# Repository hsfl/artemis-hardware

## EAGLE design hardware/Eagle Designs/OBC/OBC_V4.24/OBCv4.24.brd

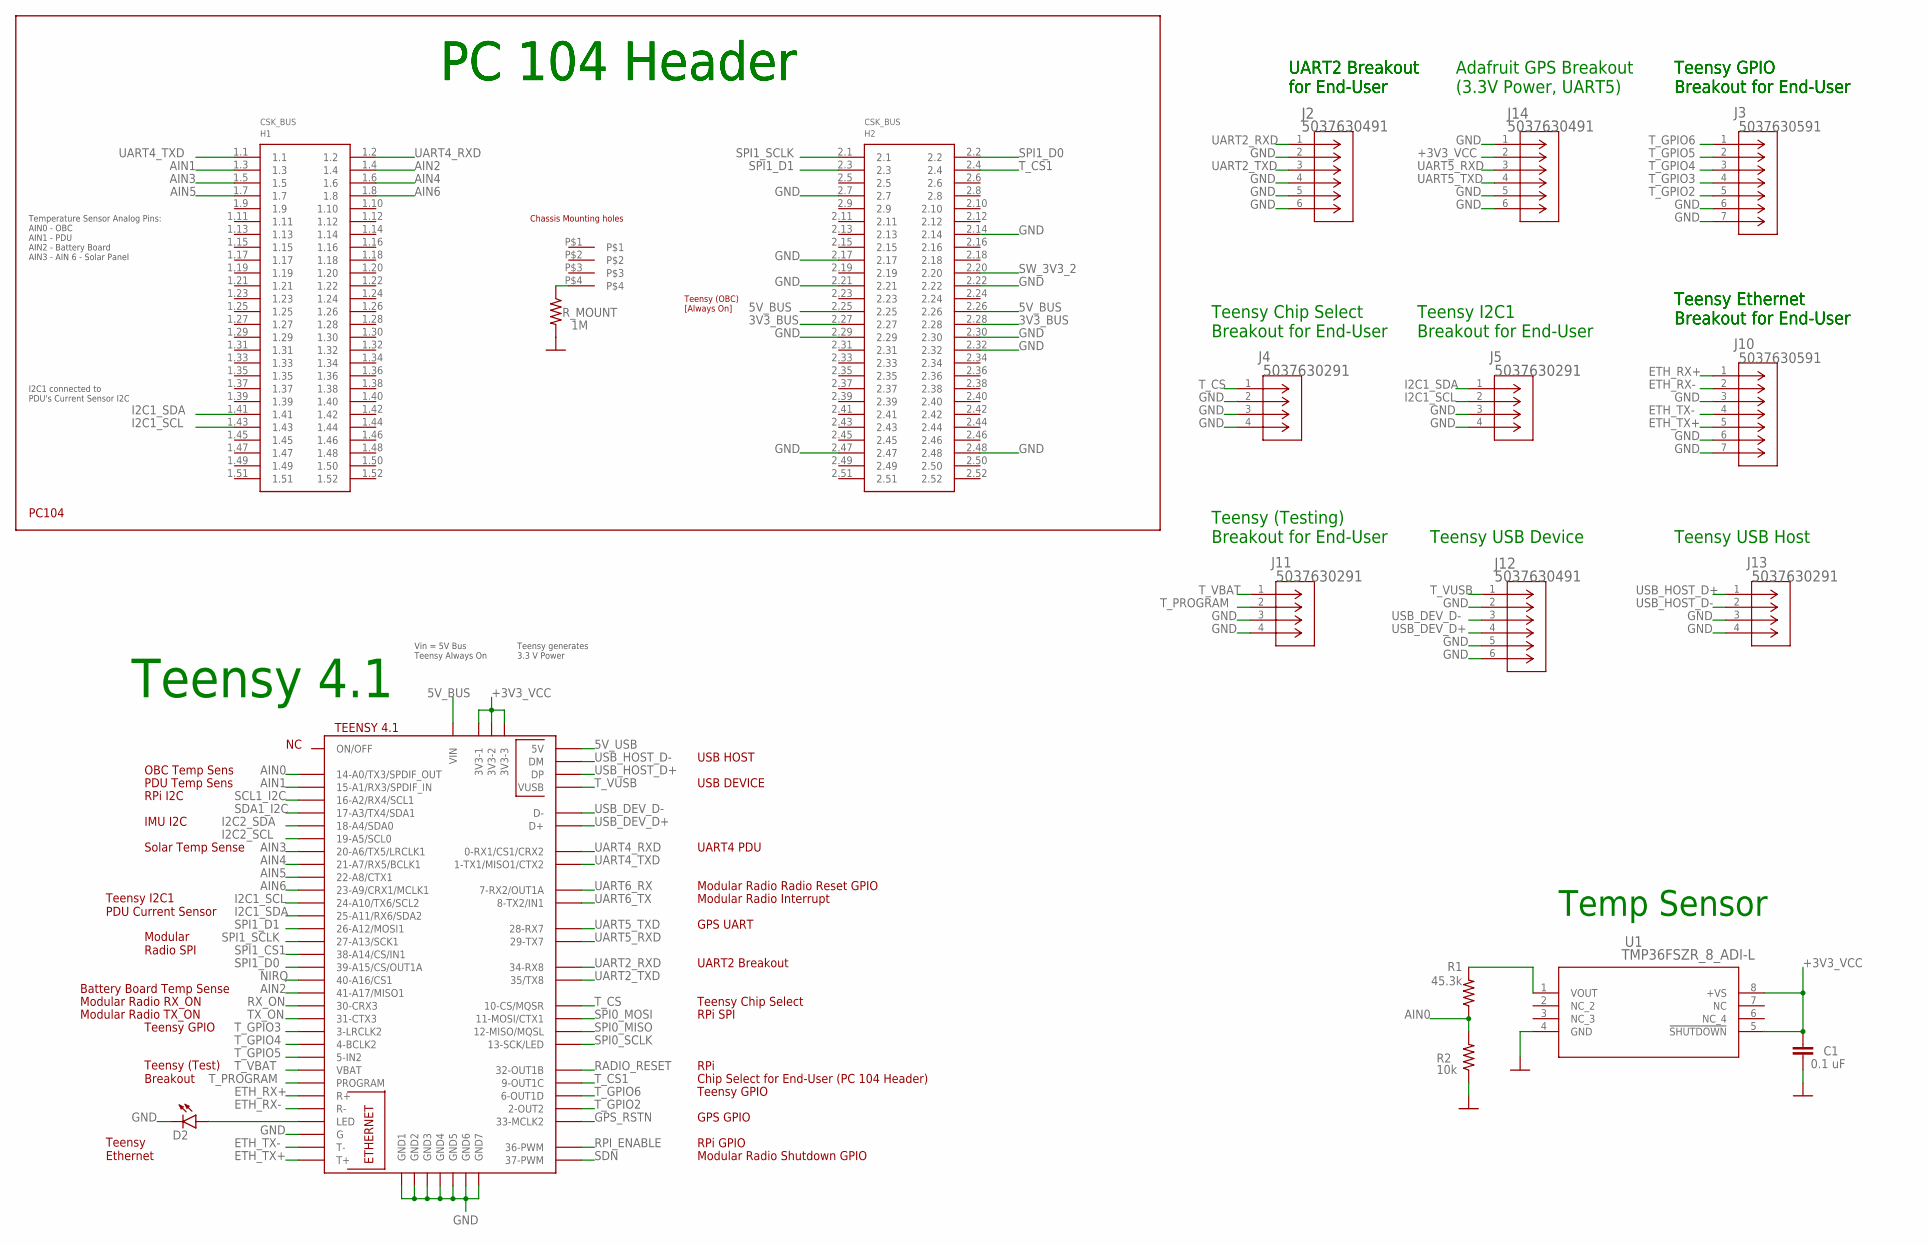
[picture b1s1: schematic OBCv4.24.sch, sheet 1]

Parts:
C1: 0.1 uF; 0805
D2: LEDCHIP-LED0603; CHIP-LED0603
H1: PC104_WCONN
J2, J12, J14: 5037630491; CON_5037630491
J3, J10: 5037630591; CON_5037630591
J4, J5, J11, J13: 5037630291; CON_5037630291
R1: 45.3k; 0805
R2: 10k; 0805
R_MOUNT: 1M; 0805
U1: TMP36FSZR_8_ADI-L; R_8_ADI-L
U$1: TEENSY41TEENSY; TEENSY41

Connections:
3V3_BUS: H1.2.27, H1.2.28; also elsewhere on the board
5V_BUS: H1.2.25, H1.2.26, U$1.VIN; also elsewhere on the board
5V_USB: U$1.+5V (5V)
+3V3_VCC: C1.1, J14.2, U1.5 (!SHUTDOWN), U1.8 (+VS), U$1.3V3-1, U$1.3V3-2, U$1.3V3-3; also elsewhere on the board
AIN0: R1.1, R2.2, U$1.14-A0/TX3/SPDIF_OUT
AIN1: H1.1.3, U$1.15-A1/RX3/SPDIF_IN
AIN2: H1.1.4, U$1.41-A17/MISO1
AIN3: H1.1.5, U$1.20-A6/TX5/LRCLK1
AIN4: H1.1.6, U$1.21-A7/RX5/BCLK1
AIN5: H1.1.7, U$1.22-A8/CTX1
AIN6: H1.1.8, U$1.23-A9/CRX1/MCLK1
ETH_RX+: J10.1, U$1.R+
ETH_RX-: J10.2, U$1.R-
ETH_TX+: J10.5, U$1.T+
ETH_TX-: J10.4, U$1.T-
GND: C1.2, D2.C, H1.2.7, H1.2.14, H1.2.17, H1.2.21, H1.2.22, H1.2.29, H1.2.30, H1.2.32, H1.2.47, H1.2.48, J2.2, J2.4, J2.5, J2.6, J3.6, J3.7, J4.2, J4.3, J4.4, J5.3, J5.4, J10.3, J10.6, J10.7, J11.3, J11.4, J12.2, J12.5, J12.6, J13.3, J13.4, J14.1, J14.5, J14.6, R2.1, R_MOUNT.2, U1.4 (GND), U$1.G, U$1.GND (GND7), U$1.GND1, U$1.GND2, U$1.GND3, U$1.GND4, U$1.GND5, U$1.GND6; also elsewhere on the board
GPS_RSTN: U$1.33-MCLK2; also elsewhere on the board
I2C1_SCL: H1.1.43, J5.2, U$1.24-A10/TX6/SCL2
I2C1_SDA: H1.1.41, J5.1, U$1.25-A11/RX6/SDA2
I2C2_SCL: U$1.19-A5/SCL0; also elsewhere on the board
I2C2_SDA: U$1.18-A4/SDA0; also elsewhere on the board
unnamed: D2.A, U$1.LED
unnamed: R1.2, U1.1 (VOUT)
unnamed: H1.P$4, R_MOUNT.1
NIRQ: U$1.40-A16/CS1; also elsewhere on the board
RADIO_RESET: U$1.32-OUT1B; also elsewhere on the board
RPI_ENABLE: U$1.36-PWM; also elsewhere on the board
RX_ON: U$1.30-CRX3; also elsewhere on the board
SCL1_I2C: U$1.16-A2/RX4/SCL1; also elsewhere on the board
SDA1_I2C: U$1.17-A3/TX4/SDA1; also elsewhere on the board
SDN: U$1.37-PWM; also elsewhere on the board
SPI0_MISO: U$1.12-MISO/MQSL; also elsewhere on the board
SPI0_MOSI: U$1.11-MOSI/CTX1; also elsewhere on the board
SPI0_SCLK: U$1.13-SCK/LED; also elsewhere on the board
SPI1_CS1: U$1.38-A14/CS/IN1; also elsewhere on the board
SPI1_D0: H1.2.2, U$1.39-A15/CS/OUT1A; also elsewhere on the board
SPI1_D1: H1.2.3, U$1.26-A12/MOSI1; also elsewhere on the board
SPI1_SCLK: H1.2.1, U$1.27-A13/SCK1; also elsewhere on the board
SW_3V3_2: H1.2.20; also elsewhere on the board
TX_ON: U$1.31-CTX3; also elsewhere on the board
T_CS: J4.1, U$1.10-CS\MQSR (10-CS/MQSR)
T_CS1: H1.2.4, U$1.9-OUT1C
T_GPIO2: J3.5, U$1.2-OUT2
T_GPIO3: J3.4, U$1.3-LRCLK2
T_GPIO4: J3.3, U$1.4-BCLK2
T_GPIO5: J3.2, U$1.5-IN2
T_GPIO6: J3.1, U$1.6-OUT1D
T_PROGRAM: J11.2, U$1.PROGRAM
T_VBAT: J11.1, U$1.VBAT
T_VUSB: J12.1, U$1.VUSB
UART2_RXD: J2.1, U$1.34-RX8
UART2_TXD: J2.3, U$1.35-TX8 (35/TX8)
UART4_RXD: H1.1.2, U$1.0-RX1/CS1/CRX2
UART4_TXD: H1.1.1, U$1.1-TX1/MISO1/CTX2
UART5_RXD: J14.3, U$1.29-TX7; also elsewhere on the board
UART5_TXD: J14.4, U$1.28-RX7; also elsewhere on the board
UART6_RX: U$1.7-RX2/OUT1A; also elsewhere on the board
UART6_TX: U$1.8-TX2/IN1; also elsewhere on the board
USB_DEV_D+: J12.4, U$1.D+
USB_DEV_D-: J12.3, U$1.D-
USB_HOST_D+: J13.1, U$1.DP
USB_HOST_D-: J13.2, U$1.DM

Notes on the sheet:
Temp Sensor
PC 104 Header
Temperature Sensor Analog Pins: AIN0 - OBC AIN1 - PDU AIN2 - Battery Board AIN3 - AIN 6 - Solar Panel
UART2 Breakout for End-User
Teensy 4.1
Teensy GPIO Breakout for End-User
Teensy Chip Select Breakout for End-User
Teensy I2C1 Breakout for End-User
OBC Temp Sens
PDU Temp Sens
RPi I2C
IMU I2C
Solar Temp Sense
Teensy I2C1 PDU Current Sensor
Modular Radio SPI
Battery Board Temp Sense
Teensy GPIO
Teensy (Test) Breakout
Teensy Ethernet
RPi GPIO
GPS GPIO
RPi SPI
Teensy Chip Select
UART2 Breakout
GPS UART
Modular Radio Radio Reset GPIO
UART4 PDU
USB HOST
USB DEVICE
Teensy Ethernet Breakout for End-User
Teensy (Testing) Breakout for End-User
Teensy USB Device
Teensy USB Host
Teensy (OBC) [Always On]
Vin = 5V Bus Teensy Always On
Teensy generates 3.3 V Power
Adafruit GPS Breakout (3.3V Power, UART5)
Modular Radio Interrupt
I2C1 connected to PDU's Current Sensor I2C
Chip Select for End-User (PC 104 Header)

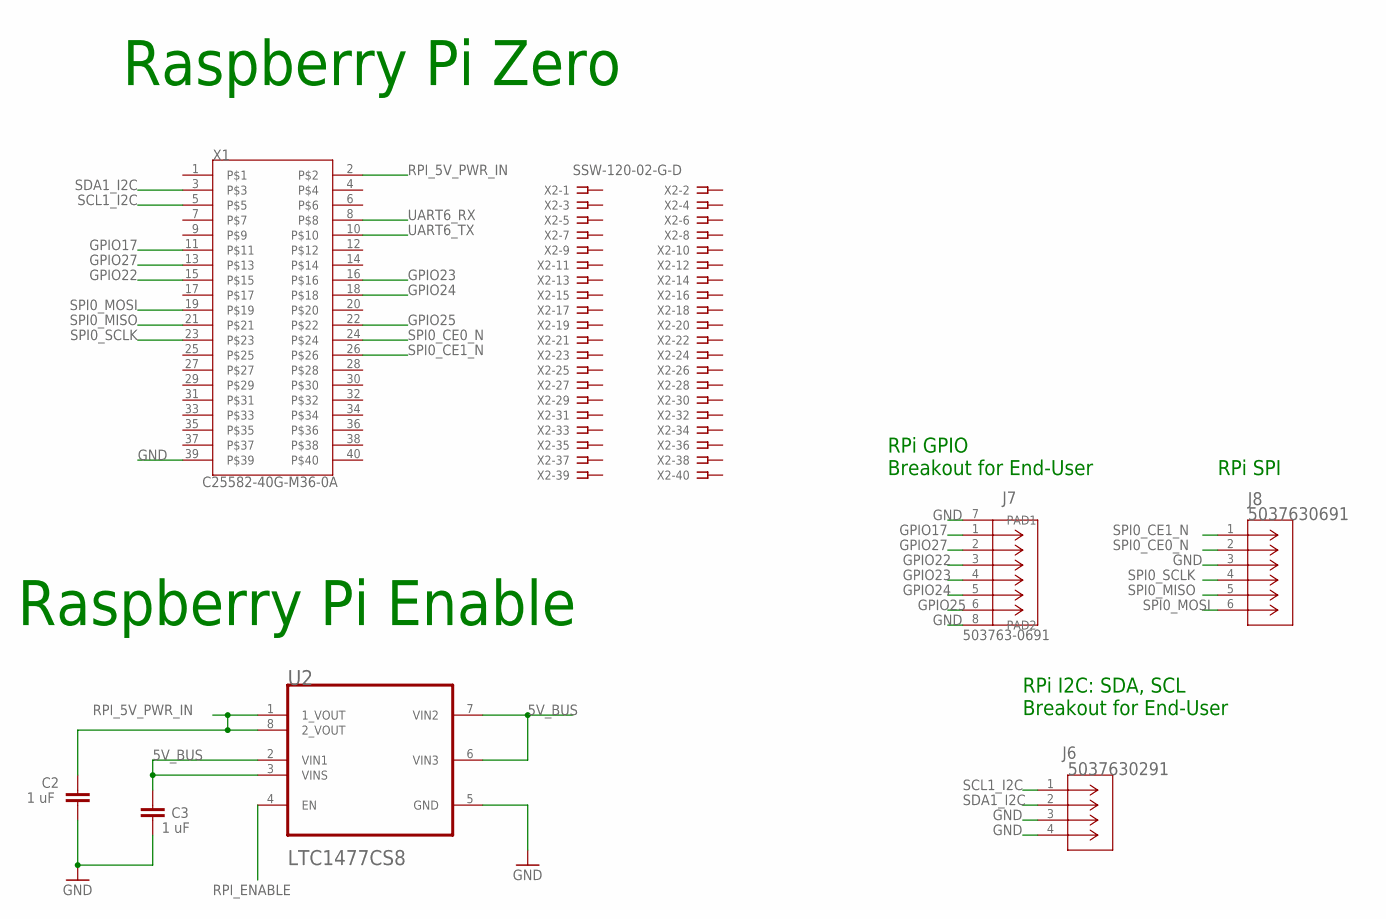
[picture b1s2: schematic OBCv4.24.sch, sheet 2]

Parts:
C2, C3: 1 uF; 0805
J6: 5037630291; CON_5037630291
J7: 503763-0691; CONN_503763-0691_MOL
J8: 5037630691; CONN_503763-0691_MOL
U2: LTC1477CS8LINEAR_TECHNOLOGY_LTC1477CS8_0_2; LINEAR_TECHNOLOGY_LTC1477CS8_2
X1: C25582-40G-M36-0A; ADAFRUIT_C25582-40G-M36-0A_0
X2: SSW-120-02-G-D

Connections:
5V_BUS: C3.1, U2.2 (VIN1), U2.3 (VINS), U2.6 (VIN3), U2.7 (VIN2); also elsewhere on the board
GND: C2.2, C3.2, J6.3, J6.4, J7.7 (PAD1), J7.8 (PAD2), J8.3, U2.5 (GND), X1.39; also elsewhere on the board
GPIO17: J7.1, X1.11
GPIO22: J7.3, X1.15
GPIO23: J7.4, X1.16
GPIO24: J7.5, X1.18
GPIO25: J7.6, X1.22
GPIO27: J7.2, X1.13
RPI_5V_PWR_IN: C2.1, U2.1 (1_VOUT), U2.8 (2_VOUT), X1.2
RPI_ENABLE: U2.4 (EN); also elsewhere on the board
SCL1_I2C: J6.1, X1.5; also elsewhere on the board
SDA1_I2C: J6.2, X1.3; also elsewhere on the board
SPI0_CE0_N: J8.2, X1.24
SPI0_CE1_N: J8.1, X1.26
SPI0_MISO: J8.5, X1.21; also elsewhere on the board
SPI0_MOSI: J8.6, X1.19; also elsewhere on the board
SPI0_SCLK: J8.4, X1.23; also elsewhere on the board
UART6_RX: X1.8; also elsewhere on the board
UART6_TX: X1.10; also elsewhere on the board

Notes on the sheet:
Raspberry Pi Zero
Raspberry Pi Enable
RPi I2C: SDA, SCL Breakout for End-User
RPi GPIO Breakout for End-User
RPi SPI

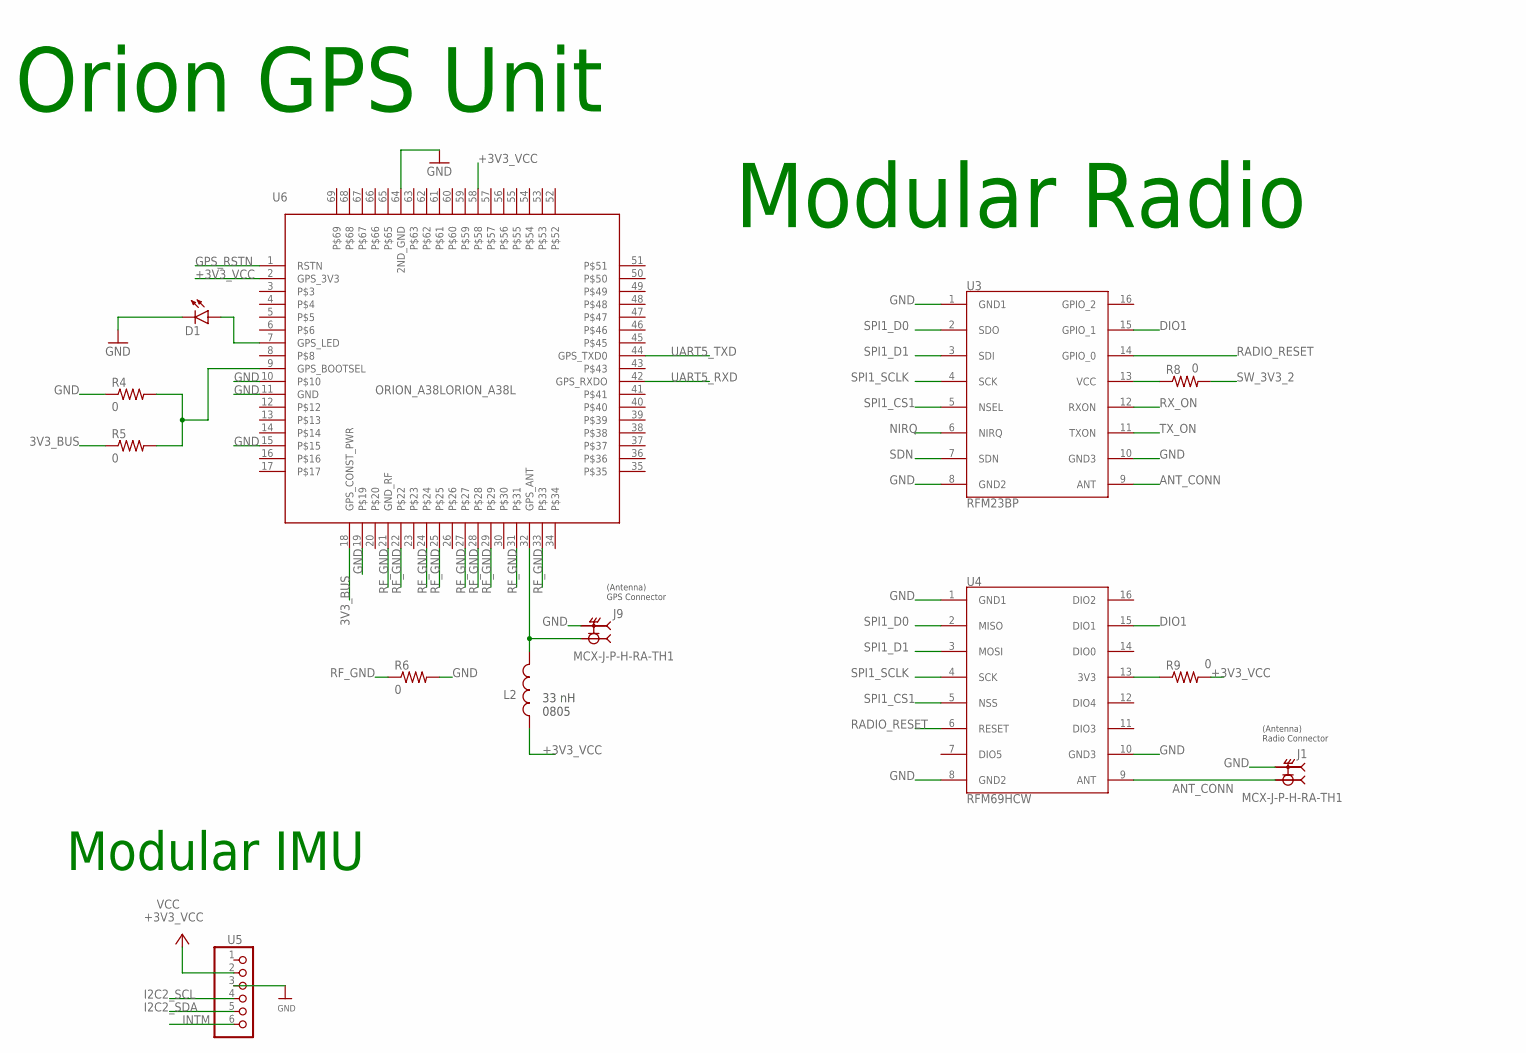
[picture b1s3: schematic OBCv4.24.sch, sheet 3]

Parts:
D1: LEDCHIP-LED0603; CHIP-LED0603
J1, J9: MCX-J-P-H-RA-TH1; SAMTEC_MCX-J-P-H-RA-TH1
L2: AIMC-0805-2N2S-T; INDC2012X105N
R4, R5, R6: 0; 0805
R8, R9: 0; R2512
U3: RFM23BP
U4: RFM69HCW
U5: HEADER-1X670MIL; 1X06_ROUND_70
U6: ORION_A38LORION_A38L; ORION_A38L

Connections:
3V3_BUS: R5.1, U6.18 (GPS_CONST_PWR); also elsewhere on the board
+3V3_VCC: L2.1, R9.2, U5.2, U6.2 (GPS_3V3), U6.58; also elsewhere on the board
ANT_CONN: J1.1, U3.9 (ANT), U4.9 (ANT)
DIO1: U3.15 (GPIO_1), U4.15 (DIO1)
GND: D1.C, J1.S1 (2), J1.S2 (2), J1.S3 (2), J1.S4 (2), J9.S1 (2), J9.S2 (2), J9.S3 (2), J9.S4 (2), R4.1, R6.2, U3.1 (GND1), U3.8 (GND2), U3.10 (GND3), U4.1 (GND1), U4.8 (GND2), U4.10 (GND3), U5.3, U6.10, U6.11 (GND), U6.15, U6.19, U6.64 (2ND_GND); also elsewhere on the board
GPS_RSTN: U6.1 (RSTN); also elsewhere on the board
I2C2_SCL: U5.4; also elsewhere on the board
I2C2_SDA: U5.5; also elsewhere on the board
INTM: U5.6
unnamed: R8.1, U3.13 (VCC)
unnamed: R9.1, U4.13 (3V3)
unnamed: R4.2, R5.2, U6.9 (GPS_BOOTSEL)
unnamed: J9.1, L2.2, U6.32 (GPS_ANT)
unnamed: D1.A, U6.7 (GPS_LED)
NIRQ: U3.6 (NIRQ); also elsewhere on the board
RADIO_RESET: U3.14 (GPIO_0), U4.6 (RESET); also elsewhere on the board
RF_GND: R6.1, U6.21 (GND_RF), U6.22, U6.24, U6.25, U6.27, U6.28, U6.29, U6.31, U6.33
RX_ON: U3.12 (RXON); also elsewhere on the board
SDN: U3.7 (SDN); also elsewhere on the board
SPI1_CS1: U3.5 (NSEL), U4.5 (NSS); also elsewhere on the board
SPI1_D0: U3.2 (SDO), U4.2 (MISO); also elsewhere on the board
SPI1_D1: U3.3 (SDI), U4.3 (MOSI); also elsewhere on the board
SPI1_SCLK: U3.4 (SCK), U4.4 (SCK); also elsewhere on the board
SW_3V3_2: R8.2; also elsewhere on the board
TX_ON: U3.11 (TXON); also elsewhere on the board
UART5_RXD: U6.42 (GPS_RXDO); also elsewhere on the board
UART5_TXD: U6.44 (GPS_TXD0); also elsewhere on the board

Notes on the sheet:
Orion GPS Unit
Modular Radio
Modular IMU
(Antenna) Radio Connector
(Antenna) GPS Connector
33 nH 0805

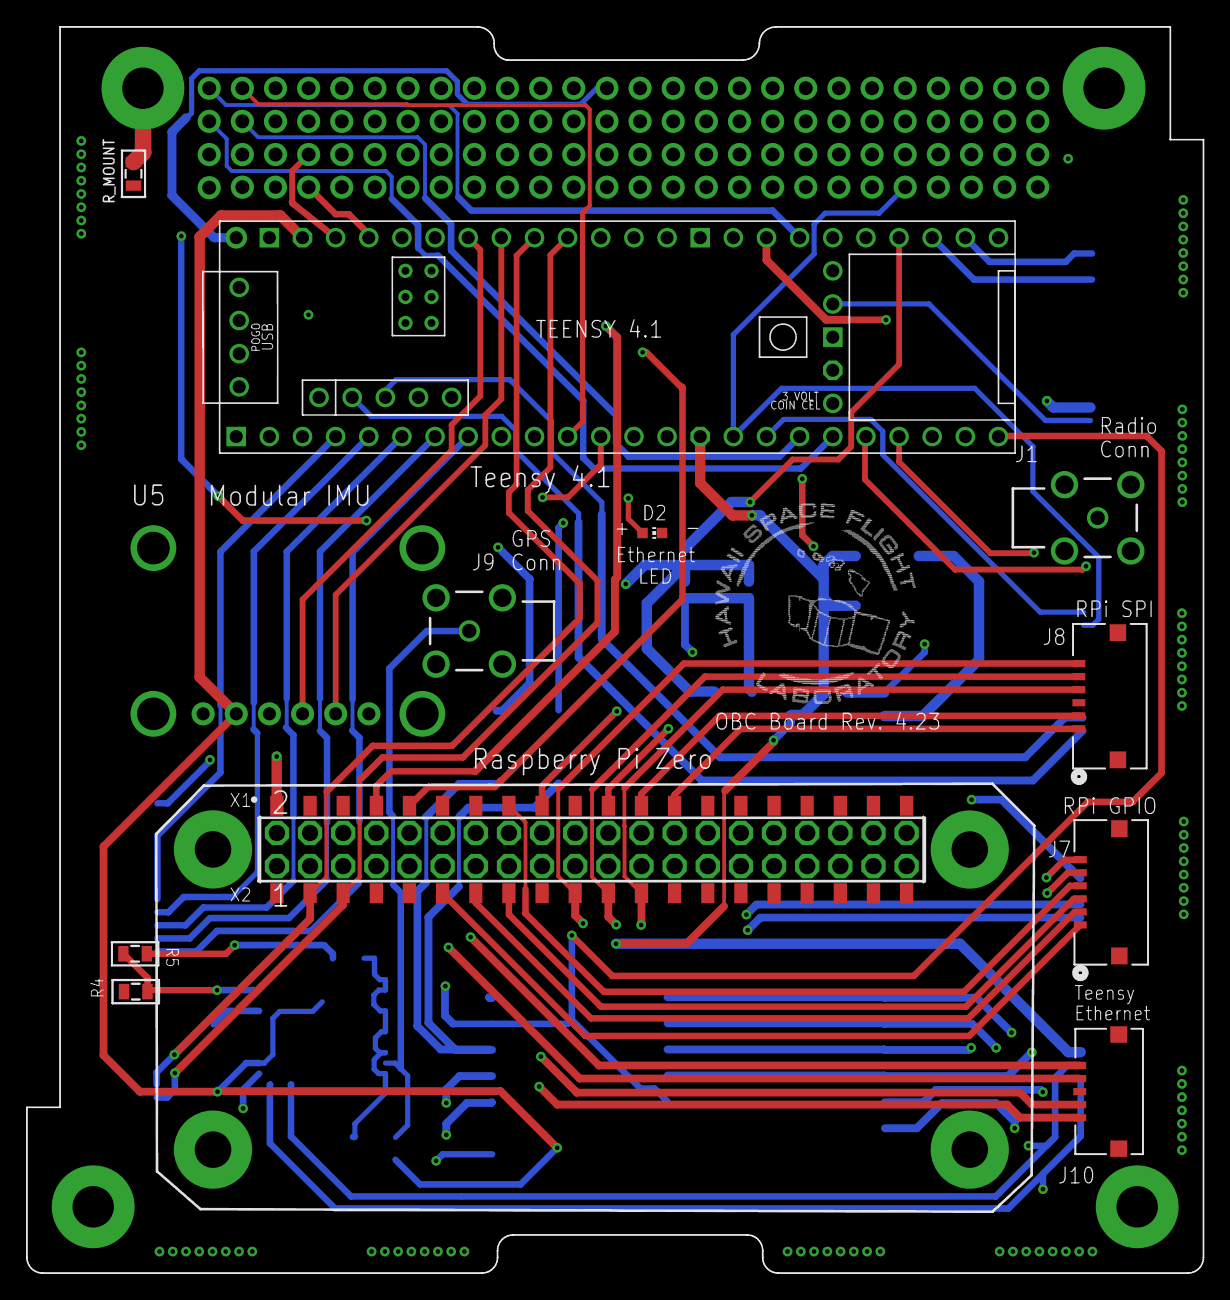
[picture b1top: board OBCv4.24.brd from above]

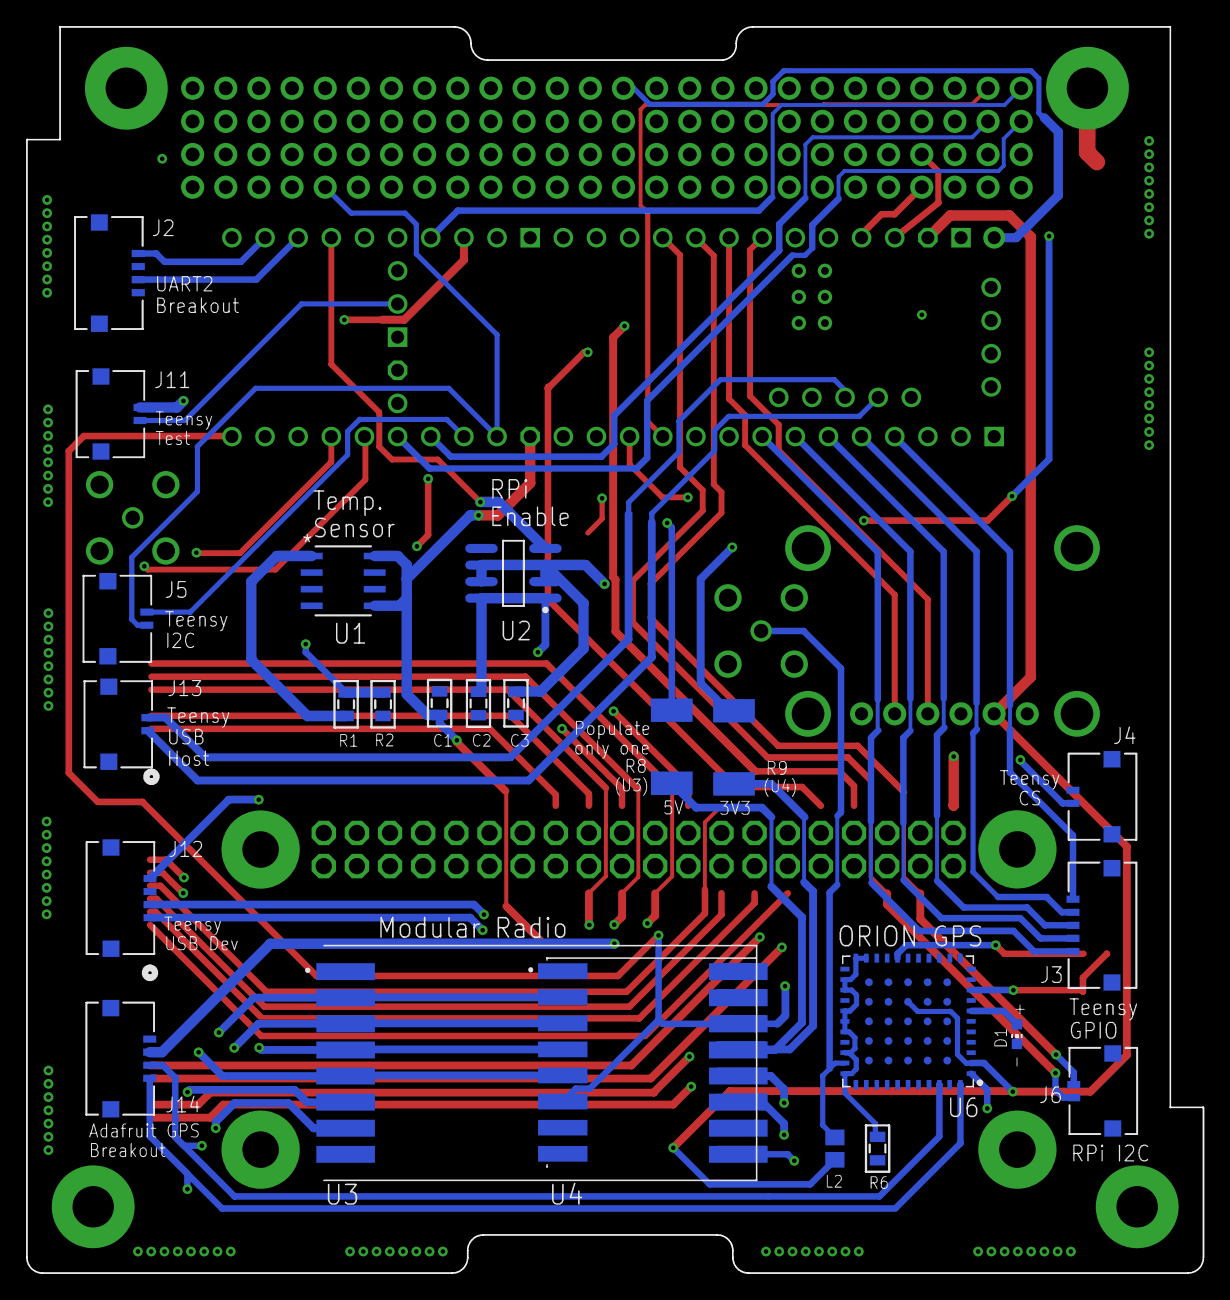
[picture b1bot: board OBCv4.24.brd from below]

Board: 4 copper layers, 90.2 x 95.5 mm, 38 parts (24 on the bottom side), 78 nets.

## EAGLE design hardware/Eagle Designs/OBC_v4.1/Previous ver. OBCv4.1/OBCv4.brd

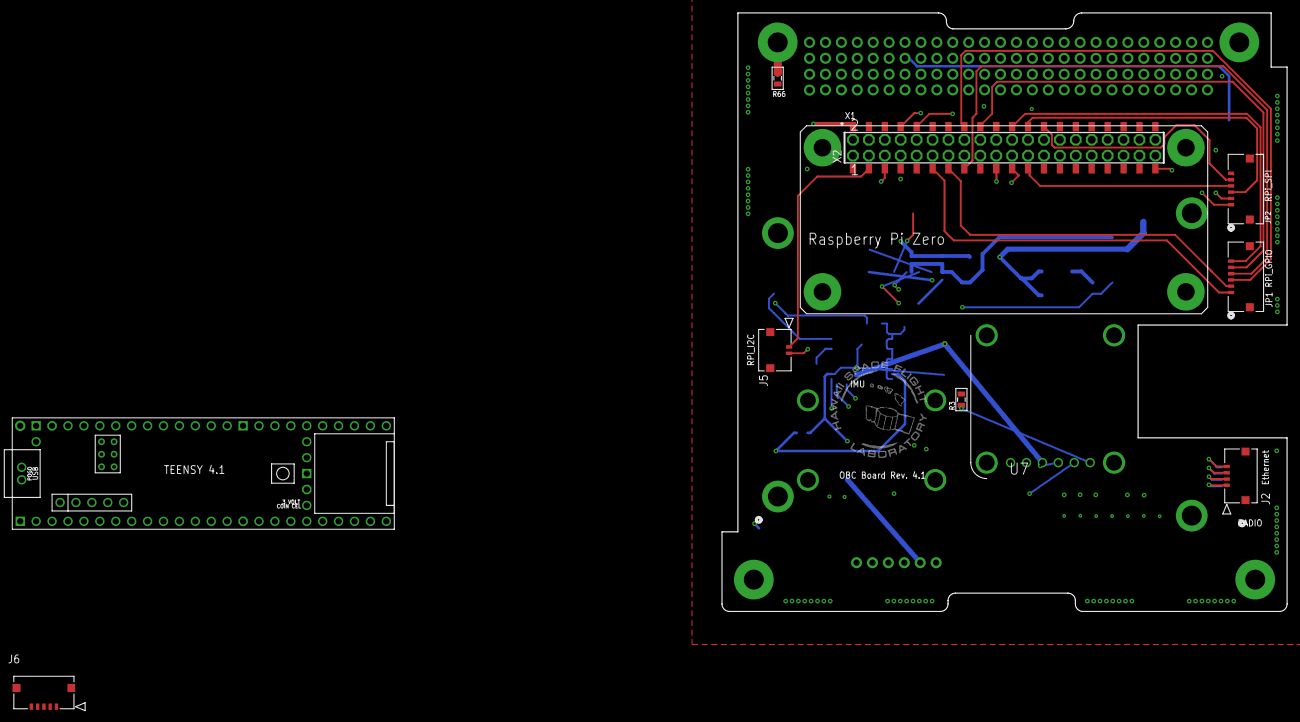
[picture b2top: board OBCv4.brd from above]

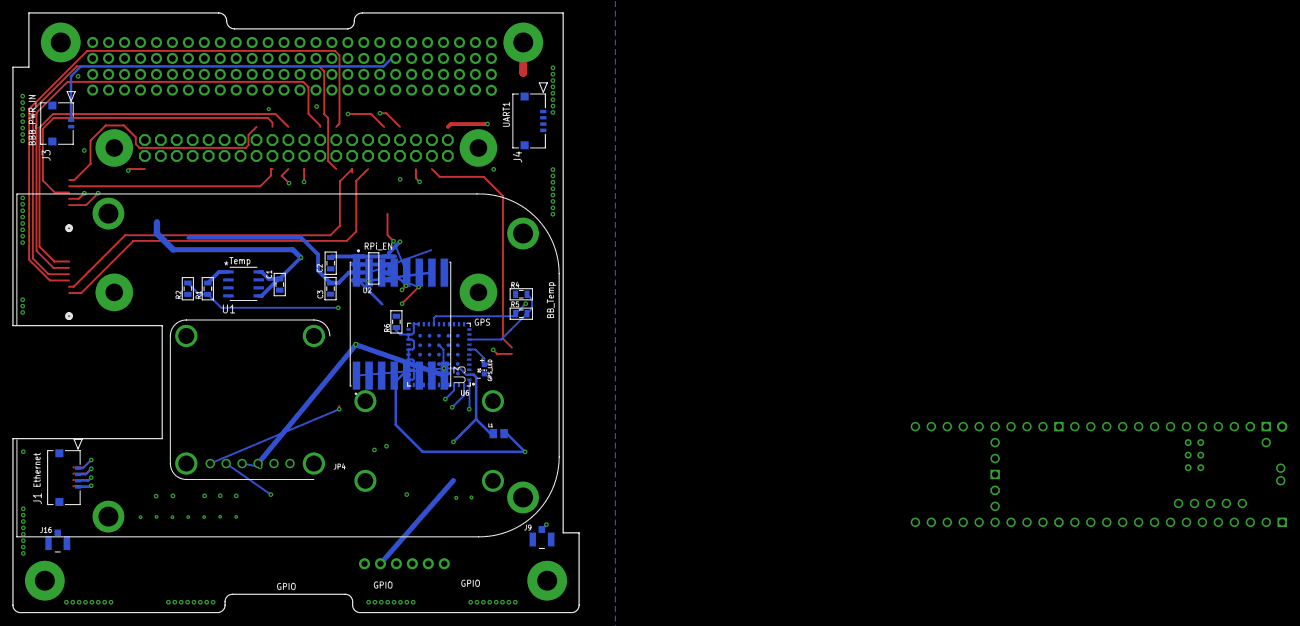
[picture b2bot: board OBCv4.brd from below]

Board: 4 copper layers, 90.2 x 95.5 mm, 32 parts (21 on the bottom side), 61 nets.

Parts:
C1: 0.1 uF; 0805
C2, C3: 1 uF; 0805
D1: CHIP-LED0603
H1: PC104_WCONN
J1, J2, J4: 5037630491; CON_5037630491
J3, J5: 5037630291; CON_5037630291
J6: 5037630591; CON_5037630591
J9, J16: U.FL-R-SMT-1(01); CONN_-SMT-1(01)
JP1, JP2: 503763-0691; CONN_503763-0691_MOL
JP4: 1X06_ROUND_70
L1: L; INDC2012X145N
R1: 45.3k; 0805
R2, R3: 10k; 0805
R4, R5, R6: 0; 0805
R66: 1M; 0805
U1: TMP36FSZR_8_ADI-L; R_8_ADI-L
U2: LTC1477CS8LINEAR_TECHNOLOGY_LTC1477CS8_0_2; LINEAR_TECHNOLOGY_LTC1477CS8_2
U3: RFM69HCW_433_900; RFM69HCW_433
U6: ORION_A38LORION_A38L; ORION_A38L
U7: PA1010D
U$1: TEENSY41
X1: C25582-40G-M36-0A; ADAFRUIT_C25582-40G-M36-0A_0
X2: SSW-120-02-G-D

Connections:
3V3_BUS: H1.2.27, H1.2.28, R5.1, U6.18
5V_BUS: H1.2.25, H1.2.26
+3V3_VCC: C1.1, JP4.2, L1.1, U1.5, U1.8, U3.16, U6.2, U6.58, U7.3, U$1.3V3-1, U$1.3V3-3
+5V_VCC: C3.1, U2.2, U2.3, U2.6, U2.7, U$1.+5V, U$1.VIN
AIN0: R1.1, R2.2, U$1.14-A0/TX3/SPDIF_OUT
AIN1: H1.1.3, U$1.15-A1/RX3/SPDIF_IN
AIN2: H1.1.4, U$1.41-A17/MISO1
AIN3: H1.1.5, U$1.20-A6/TX5/LRCLK1
AIN4: H1.1.6, U$1.21-A7/RX5/BCLK1
AIN5: H1.1.7, U$1.22-A8/CTX1
AIN6: H1.1.8, U$1.23-A9/CRX1/MCLK1
GND: C1.2, C2.2, C3.2, D1.C, H1.2.7, H1.2.14, H1.2.17, H1.2.21, H1.2.22, H1.2.29, H1.2.30, H1.2.32, H1.2.47, H1.2.48, J1.5, J1.6, J2.5, J2.6, J3.2, J3.3, J3.4, J4.2, J4.4, J4.5, J4.6, J5.3, J5.4, J6.6, J6.7, J9.1, J9.2, J16.1, J16.2, JP1.7, JP1.8, JP2.6, JP2.7, JP2.8, JP4.3, R2.1, R3.2, R4.1, R6.2, R66.2, U1.4, U2.5, U3.6, U3.8, U6.10, U6.11, U6.15, U6.19, U6.64, U7.1, U$1.GND1, U$1.GND2, U$1.GND3, U$1.GND4, U$1.GND5, U$1.GND6, X1.39
GPIO17: JP1.1, X1.11
GPIO22: JP1.4, X1.15
GPIO23: JP1.3, X1.16
GPIO24: JP1.5, X1.18
GPIO25: JP1.6, X1.22
GPIO27: JP1.2, X1.13
GPS_RSTN: U6.1, U$1.33-MCLK2
I2C2_SCL: JP4.4, U$1.19-A5/SCL0
I2C2_SDA: JP4.5, U$1.18-A4/SDA0
unnamed: J16.3, U3.7
unnamed: R1.2, U1.1
unnamed: R4.2, R5.2, U6.9
unnamed: J9.3, L1.2, U6.32
unnamed: R3.1, U7.6
unnamed: D1.A, U6.7
unnamed: H1.P$4, R66.1
RADIO_RESET: U3.9, U$1.7-RX2/OUT1A
RF_GND: R6.1, U6.21, U6.22, U6.24, U6.25, U6.27, U6.28, U6.29, U6.31, U6.33
RPI_5V_PWR_IN: C2.1, U2.1, U2.8, X1.2
RPI_ENABLE: U2.4, U$1.36-PWM
RX+: J1.3, J2.2
RX-: J1.4, J2.1
SCL1_I2C: J5.2, X1.5
SDA1_I2C: J5.1, X1.3
SPI0_CE0_N: JP2.3, X1.24
SPI0_CE1_N: JP2.5, X1.26
SPI0_MISO: JP2.2, U$1.12-MISO/MQSL, X1.21
SPI0_MOSI: JP2.1, U$1.11-MOSI/CTX1, X1.19
SPI0_SCLK: JP2.4, U$1.13-SCK/LED, X1.23
SPI1_CS1: U3.2, U$1.38-A14/CS/IN1
SPI1_D0: U3.4, U$1.39-A15/CS/OUT1A
SPI1_D1: U3.3, U$1.26-A12/MOSI1
SPI1_SCLK: U3.5, U$1.27-A13/SCK1
SW_5V_1: H1.2.13, J3.1
TX+: J1.1, J2.4
TX-: J1.2, J2.3
T_GPIO2: J6.1, U$1.2-OUT2
T_GPIO3: J6.2, U$1.3-LRCLK2
T_GPIO4: J6.3, U$1.4-BCLK2
T_GPIO5: J6.4, U$1.5-IN2
T_GPIO6: J6.5, U$1.6-OUT1D
UART1_RXD: J4.1, U$1.34-RX8
UART1_TXD: J4.3, U$1.35-TX8
UART2_RXD: U$1.0-RX1/CS1/CRX2, X1.8
UART2_TXD: U$1.1-TX1/MISO1/CTX2, X1.10
UART4_RXD: H1.1.1, U$1.16-A2/RX4/SCL1
UART4_TXD: H1.1.2, U$1.17-A3/TX4/SDA1
UART5_RXD: U6.44, U7.4, U$1.28-RX7
UART5_TXD: U6.42, U7.5, U$1.29-TX7

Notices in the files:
parts and their libraries:
SparkFun-PowerSymbols: Licensing: Creative Commons ShareAlike 4.0 International - https://creativecommons.org/licenses/by-sa/4.0
Improved Molex 503763-0691: COPYRIGHT: Copyright (C) 2018 Accelerated Designs. All rights reserved
COPYRIGHT: Copyright (C) 2021 Ultra Librarian. All rights reserved.
